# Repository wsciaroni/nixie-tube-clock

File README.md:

# nixie-tube-clock
Work in progress for designing and building a custom Nixie Tube Clock

## Starting Point

This project is incomplete.

I have started from the really helpful blog here: https://crystal.uta.edu/~burns/project_nixieclock.html

## Overview

I remember my first exposure to Nixie Tubes vividly. It was an old coin counting machine we were using for a change colection fund raiser. I was fascinated by the Nixie Tubes and have never forgotten them.

After observing many other Nixie Clock builds, I decided there wasn't one that met all of my needs.

The closest that I found was here: https://crystal.uta.edu/~burns/project_nixieclock.html. However, I would like a more accurate time. So, I plan to start with this project and modify it.  My goal is to

- Remove the LEDs (I don't really want a backlight)
- Change the embedded system to an ESP8266 / NodeMCU with WiFi to maintain time with the network
- Make sure the programming port is accessible so that I can reprogram or update the firmwware as needed

My Requirements for the clock are as follows

1. The clock needs to use Nixie Tubes
2. The Clock would sync with WiFi to keep a very accurate time
3. The high voltage supply's circuitry will be it's own board for modularity
4. It will be a 6 digit 24-hour clock (H1 H0 : M1 M0 : S1 S0)
5. The clock should be powered via 120V AC

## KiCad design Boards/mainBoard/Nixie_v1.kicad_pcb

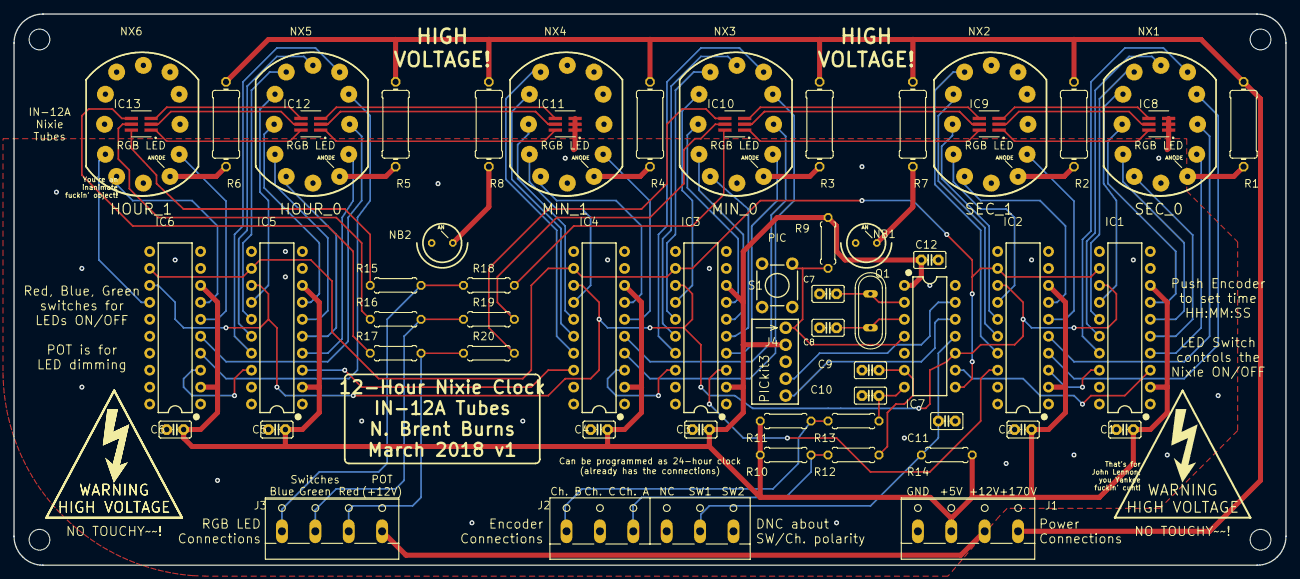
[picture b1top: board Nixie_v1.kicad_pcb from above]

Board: 2 copper layers, 190.5 x 82.6 mm, 66 parts (0 on the bottom side), 96 nets.

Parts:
@HOLE0, @HOLE1, @HOLE2, @HOLE3: (no value)
C1, C2, C3, C4, C5, C6, C11, C12: 0.1uF; C2.5-2
C7, C8: 18pF; C2.5-2
C9, C10: 0.01uF; C2.5-2
IC1, IC2, IC3, IC4, IC5, IC6: TPIC6595N; DIP20
IC7: PIC16F15325; DIP14
IC8, IC9, IC10, IC11, IC12, IC13: LED-RGB_CLY6D-FKC-CK1N1D1BB7D3D3; PLCC6-LED-RGB
J1: Screw Terminal 4 Pin; SCREW_TERM_5MM_1X4
J2: CONNECTOR_6PINSCREW_TERMINAL_5MM_PITCH; SCREW_TERM_5MM_1X6
J3: RGB Switches and 5k POT Connections; SCREW_TERM_5MM_1X4
J4: PICkit 3 Programmer; HEADER_2.54MM_1X5
NB1, NB2: IN-3
NX1, NX2, NX3, NX4, NX5, NX6: NIXIE_IN-12A; IN-12_NO_HOLE
Q1: 12.288MHz; QS
R1, R2, R3, R4, R5, R6: 14k; 0411_12
R7, R8: 162k; 0411_12
R9, R10, R11, R12, R13, R14: 10k; 0207_7
R15, R18: 300; 0207_7
R16, R19: 390; 0207_7
R17, R20: 576; 0207_7
S1: !MCLR! Reset; TACTILE_SWITCH_PTH_6.0MM
SYM101: SYMBOL_HIGH_VOLTAGE
U$3, U$6: SYMBOL_HIGH_VOLTAGE

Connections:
+5V: C1.2, C2.2, C3.2, C4.2, C5.2, C6.2, C12.1, IC1.2, IC1.8, IC2.2, IC2.8, IC3.2, IC3.8, IC4.2, IC4.8, IC5.2, IC5.8, IC6.2, IC6.8, IC7.1, J1.2, J4.2, R9.2, R10.2, R11.2, R14.1
+12V: J1.3, J3.4
+170V: J1.4, R1.1, R2.1, R3.1, R4.1, R5.1, R6.1, R7.2, R8.2
GND: C1.1, C2.1, C3.1, C4.1, C5.1, C6.1, C7.2, C8.2, C9.2, C10.2, C11.1, C12.2, IC1.1, IC1.9, IC1.10, IC1.11, IC1.19, IC1.20, IC2.1, IC2.9, IC2.10, IC2.11, IC2.19, IC2.20, IC3.1, IC3.9, IC3.10, IC3.11, IC3.19, IC3.20, IC4.1, IC4.9, IC4.10, IC4.11, IC4.19, IC4.20, IC5.1, IC5.9, IC5.10, IC5.11, IC5.19, IC5.20, IC6.1, IC6.9, IC6.10, IC6.11, IC6.19, IC6.20, IC7.14, IC8.1, IC8.2, IC8.3, IC11.1, IC11.2, IC11.3, J1.1, J2.2, J2.6, J4.3, NB1.K, NB2.K, S1.3
unnamed: IC1.4, NX1.0
unnamed: IC1.5, NX1.1
unnamed: IC1.6, NX1.2
unnamed: IC1.7, NX1.3
unnamed: IC1.14, NX1.4
unnamed: IC1.15, NX1.5
unnamed: IC1.16, NX1.6
unnamed: IC1.17, NX1.7
unnamed: NX1.A, R1.2
unnamed: NB2.A, R8.1
unnamed: NX2.A, R2.2
unnamed: NB1.A, R7.1
unnamed: NX3.A, R3.2
unnamed: NX4.A, R4.2
unnamed: NX5.A, R5.2
unnamed: NX6.A, R6.2
unnamed: IC5.4, NX5.0
unnamed: IC5.5, NX5.1
unnamed: IC2.4, NX1.8
unnamed: IC2.5, NX1.9
unnamed: IC7.12, J4.5
unnamed: IC2.6, NX2.0
unnamed: IC2.7, NX2.1
unnamed: IC2.15, NX2.3
unnamed: IC2.16, NX2.4
unnamed: IC2.17, NX2.5
unnamed: IC3.4, NX3.0
unnamed: IC3.5, NX3.1
unnamed: IC3.6, NX3.2
unnamed: IC3.7, NX3.3
unnamed: IC3.14, NX3.4
unnamed: IC3.15, NX3.5
unnamed: IC3.16, NX3.6
unnamed: IC3.17, NX3.7
unnamed: IC4.4, NX3.8
unnamed: IC4.5, NX3.9
unnamed: C7.1, IC7.2, Q1.2
unnamed: C8.1, IC7.3, Q1.1
unnamed: IC7.13, J4.4
unnamed: IC4.15, NX4.3
unnamed: IC4.16, NX4.4
unnamed: IC4.17, NX4.5
unnamed: IC5.6, NX5.2
unnamed: IC5.7, NX5.3
unnamed: IC5.14, NX5.4
unnamed: IC5.15, NX5.5
unnamed: IC5.16, NX5.6
unnamed: IC5.17, NX5.7
unnamed: IC6.4, NX5.8
unnamed: IC6.5, NX5.9
unnamed: IC6.6, NX6.0
unnamed: IC6.7, NX6.1
unnamed: IC5.18, IC6.3
unnamed: IC4.18, IC5.3
unnamed: IC3.18, IC4.3
unnamed: IC2.18, IC3.3
unnamed: IC1.18, IC2.3
unnamed: IC1.12, IC2.12, IC3.12, IC4.12, IC5.12, IC6.12, IC7.8
unnamed: IC2.14, NX2.2
unnamed: IC1.13, IC2.13, IC3.13, IC4.13, IC5.13, IC6.13, IC7.10
unnamed: IC1.3, IC7.9
unnamed: IC4.14, NX4.2
unnamed: IC4.7, NX4.1
unnamed: IC4.6, NX4.0
unnamed: IC7.4, J4.1, R9.1, S1.1
unnamed: IC6.14, NX6.2
unnamed: C11.2, IC7.11, J2.5, R14.2
unnamed: C10.1, IC7.7, R13.1
unnamed: IC12.6, IC13.1
unnamed: IC11.6, IC12.1
unnamed: IC8.6, IC9.1
unnamed: IC9.6, IC10.1
unnamed: IC12.5, IC13.2
unnamed: IC11.5, IC12.2
unnamed: IC11.4, IC12.3
unnamed: IC12.4, IC13.3
unnamed: IC9.5, IC10.2
unnamed: IC8.5, IC9.2
unnamed: IC8.4, IC9.3
unnamed: IC9.4, IC10.3
unnamed: J2.3, R10.1, R12.2
unnamed: J2.1, R11.1, R13.2
unnamed: C9.1, IC7.6, R12.1
unnamed: J3.1, R15.1, R18.1
unnamed: J3.2, R16.1, R19.1
unnamed: J3.3, R17.1, R20.1
unnamed: IC13.6, R15.2
unnamed: IC13.5, R16.2
unnamed: IC13.4, R17.2
unnamed: IC10.6, R18.2
unnamed: IC10.5, R19.2
unnamed: IC10.4, R20.2

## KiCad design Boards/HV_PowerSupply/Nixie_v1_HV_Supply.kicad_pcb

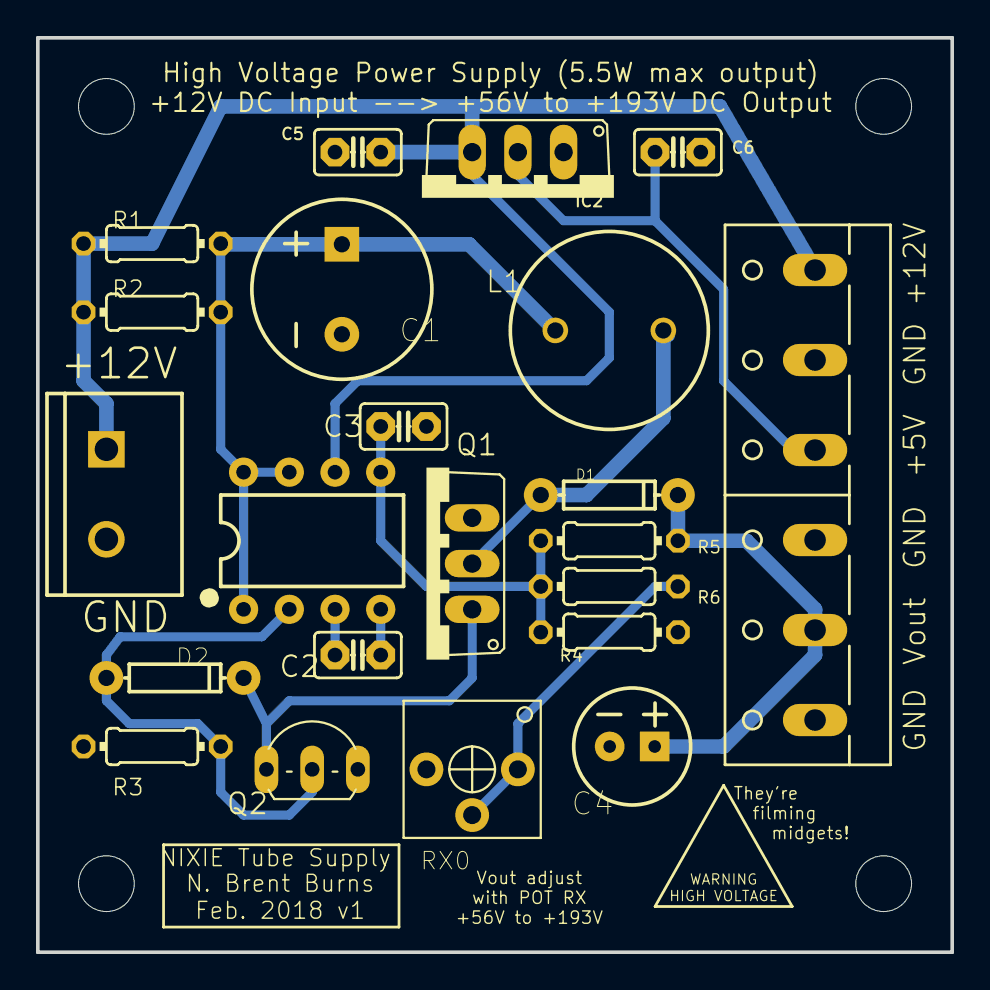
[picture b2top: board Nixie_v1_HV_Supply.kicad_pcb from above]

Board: 2 copper layers, 50.8 x 50.8 mm, 26 parts (0 on the bottom side), 11 nets.

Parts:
@HOLE0, @HOLE1, @HOLE2, @HOLE3: (no value)
C1: 220uF; CPOL-RADIAL-5MM-10MM
C2: 680pF; C2.5-2
C3: 0.01uF; C2.5-2
C4: 2.2uF; CPOL-RADIAL-2.5MM-6.5MM
C5: 0.1uF; C2.5-2
C6: 10uF; C2.5-2
D1: BAV21; DIODE-1N4148
D2: 1N914; DIODE-1N4148
IC1: MC34063AP; DIP08
IC2: LD1117V50; TO220V
J1: Screw Terminal 2 Pin; SCREW_TERM_5MM_1X2
J2: Screw Terminal 6 Pin; SCREW_TERM_5MM_1X6
L1: 150uH; INDUCTOR_11MM_DIAM_6MM_PITCH
Q1: IRF630; TO220V
Q2: MPSA55; TO92-
R1, R2: 0.5; 0204_7
R3: 1k; 0204_7
R4: 13.7k; 0204_7
R5: 475k; 0204_7
R6: 4.02k; 0204_7
RX0: 50k; TRIM_POT_PTH

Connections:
GND: C1.-, C2.2, C3.2, C4.2, C5.2, C6.2, IC1.4, IC2.1, J1.2, J2.1, J2.3, J2.5, Q1.3, Q2.3, R3.1, R4.1, RX0.1
unnamed: C6.1, IC2.2, J2.4
unnamed: D1.A, L1.2, Q1.2
unnamed: C4.1, D1.C, J2.2, R5.2
unnamed: C2.1, IC1.3
unnamed: C3.1, IC1.5, R4.2, R5.1, R6.1
unnamed: C1.+, IC1.1, IC1.7, IC1.8, L1.1, R1.2, R2.2
unnamed: R6.2, RX0.2, RX0.3
unnamed: D2.A, IC1.2, Q2.2, R3.2
unnamed: D2.C, Q1.1, Q2.1
VCC: C5.1, IC1.6, IC2.3, J1.1, J2.6, R1.1, R2.1

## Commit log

2023-01-11 Update README.md
    Add starting info
2023-01-11 Add Starting Project files
2023-01-11 Import Boards into KiCad from EAGLE
2023-01-11 Remove unused symbols from Schematic
